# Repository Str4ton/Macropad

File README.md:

# Macropad
A 12-key macropad with 2 rotary encoders using the Arduino Leonardo Micro Pro microcontroler, designed in KiCad.

The schematic can be found in the [MacroPad.pdf](https://github.com/Str4ton/Macropad/blob/main/MacroPad.pdf) file.

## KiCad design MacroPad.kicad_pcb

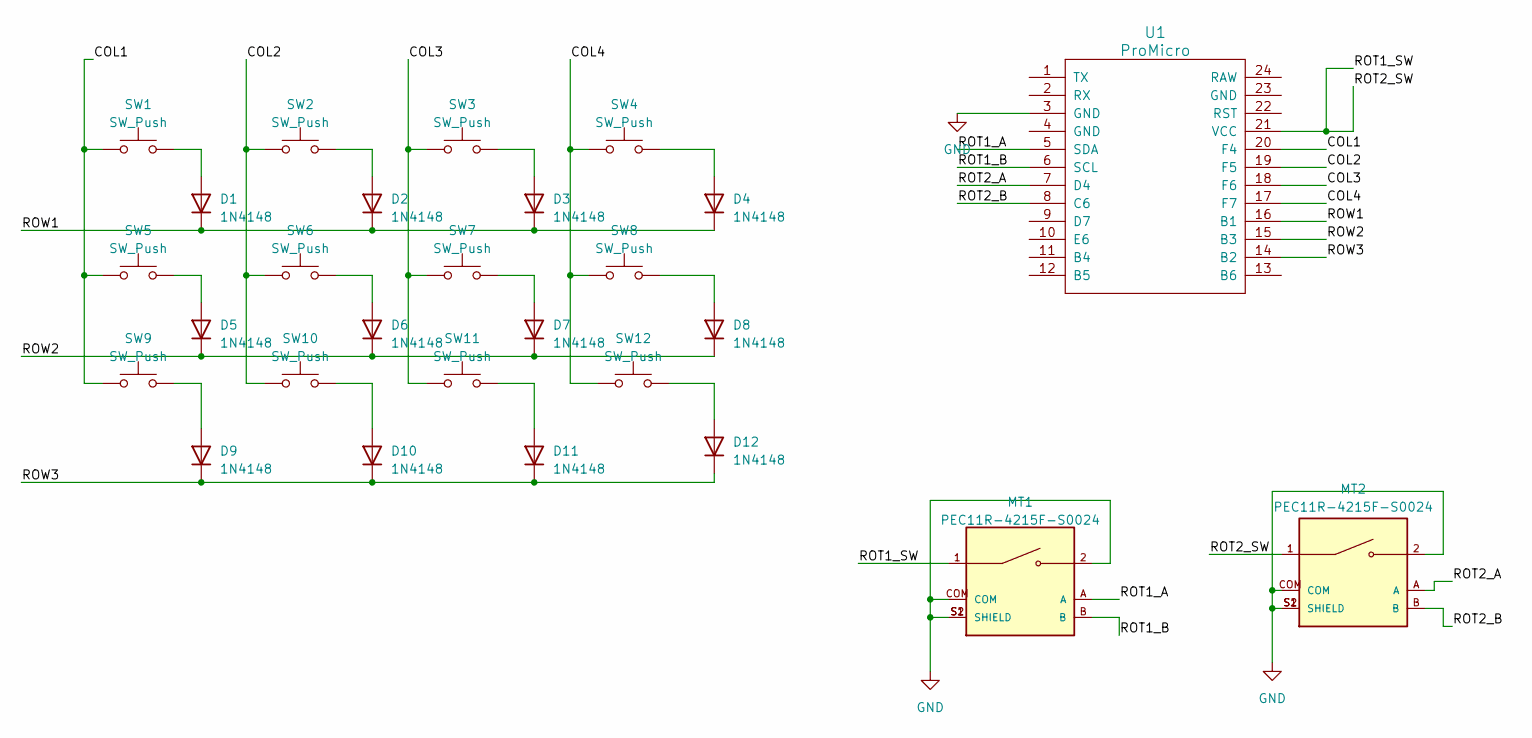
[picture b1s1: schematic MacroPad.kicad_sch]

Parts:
D1, D2, D3, D4, D5, D6, D7, D8, D9, D10, D11, D12: 1N4148; D_DO-35_SOD27_P7.62mm_Horizontal
MT1, MT2: PEC11R-4215F-S0024; XDCR_PEC11R-4215F-S0024; PARTREV Rev. 09/19
SW1, SW2, SW3, SW4, SW5, SW6, SW7, SW8, SW9, SW10, SW11, SW12: SW_Push; SW_Cherry_MX_1.00u_Plate
U1: ProMicro

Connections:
/COL1: SW1.1, SW5.1, SW9.1, U1.20 (F4)
/COL2: SW2.1, SW6.1, SW10.1, U1.19 (F5)
/COL3: SW3.1, SW7.1, SW11.1, U1.18 (F6)
/COL4: SW4.1, SW8.1, SW12.1, U1.17 (F7)
/ROT1_A: MT1.A, U1.5 (SDA)
/ROT1_B: MT1.B, U1.6 (SCL)
/ROT1_SW: MT1.1, MT2.1, U1.21 (VCC)
/ROT2_A: MT2.A, U1.7 (D4)
/ROT2_B: MT2.B, U1.8 (C6)
/ROW1: D1.1 (K), D2.1 (K), D3.1 (K), D4.1 (K), U1.16 (B1)
/ROW2: D5.1 (K), D6.1 (K), D7.1 (K), D8.1 (K), U1.15 (B3)
/ROW3: D9.1 (K), D10.1 (K), D11.1 (K), D12.1 (K), U1.14 (B2)
GND: MT1.2, MT1.COM, MT1.S1 (SHIELD), MT1.S2 (SHIELD), MT2.2, MT2.COM, MT2.S1 (SHIELD), MT2.S2 (SHIELD), U1.3 (GND)
unnamed: D1.2 (A), SW1.2
unnamed: D2.2 (A), SW2.2
unnamed: D3.2 (A), SW3.2
unnamed: D4.2 (A), SW4.2
unnamed: D5.2 (A), SW5.2
unnamed: D6.2 (A), SW6.2
unnamed: D7.2 (A), SW7.2
unnamed: D8.2 (A), SW8.2
unnamed: D9.2 (A), SW9.2
unnamed: D10.2 (A), SW10.2
unnamed: D11.2 (A), SW11.2
unnamed: D12.2 (A), SW12.2

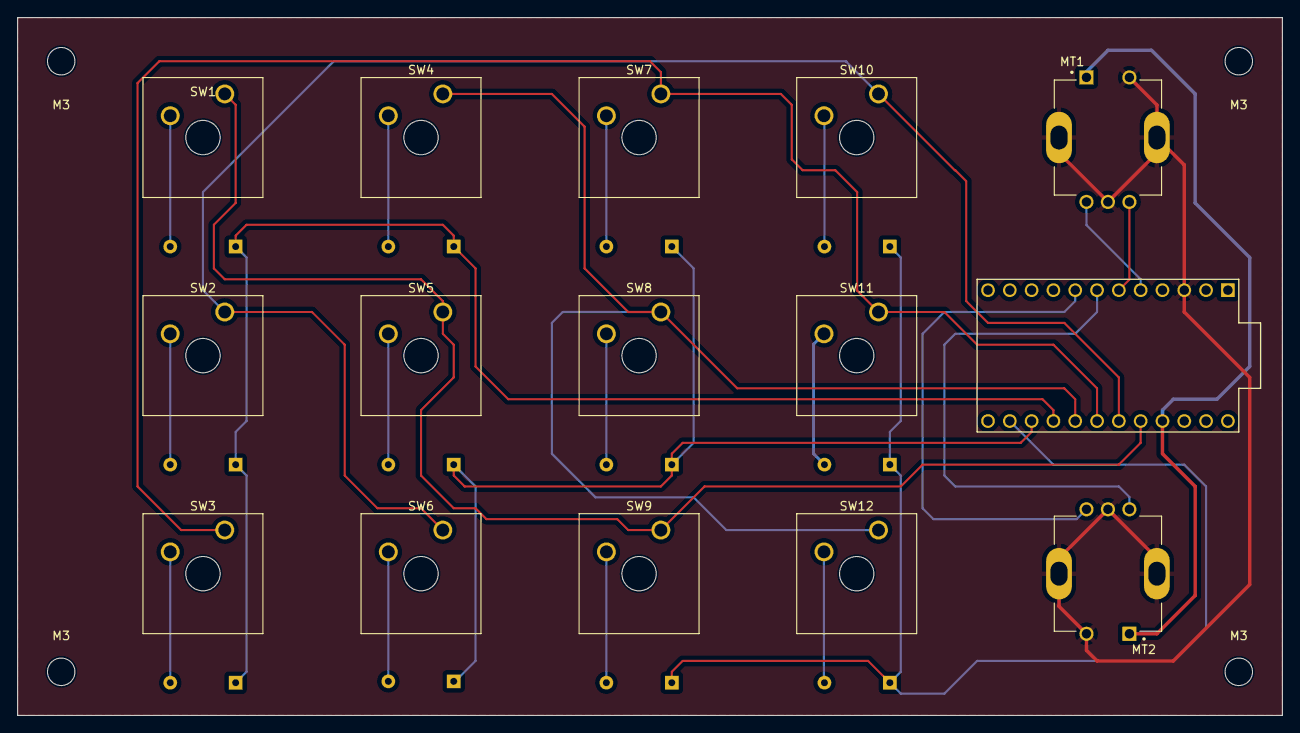
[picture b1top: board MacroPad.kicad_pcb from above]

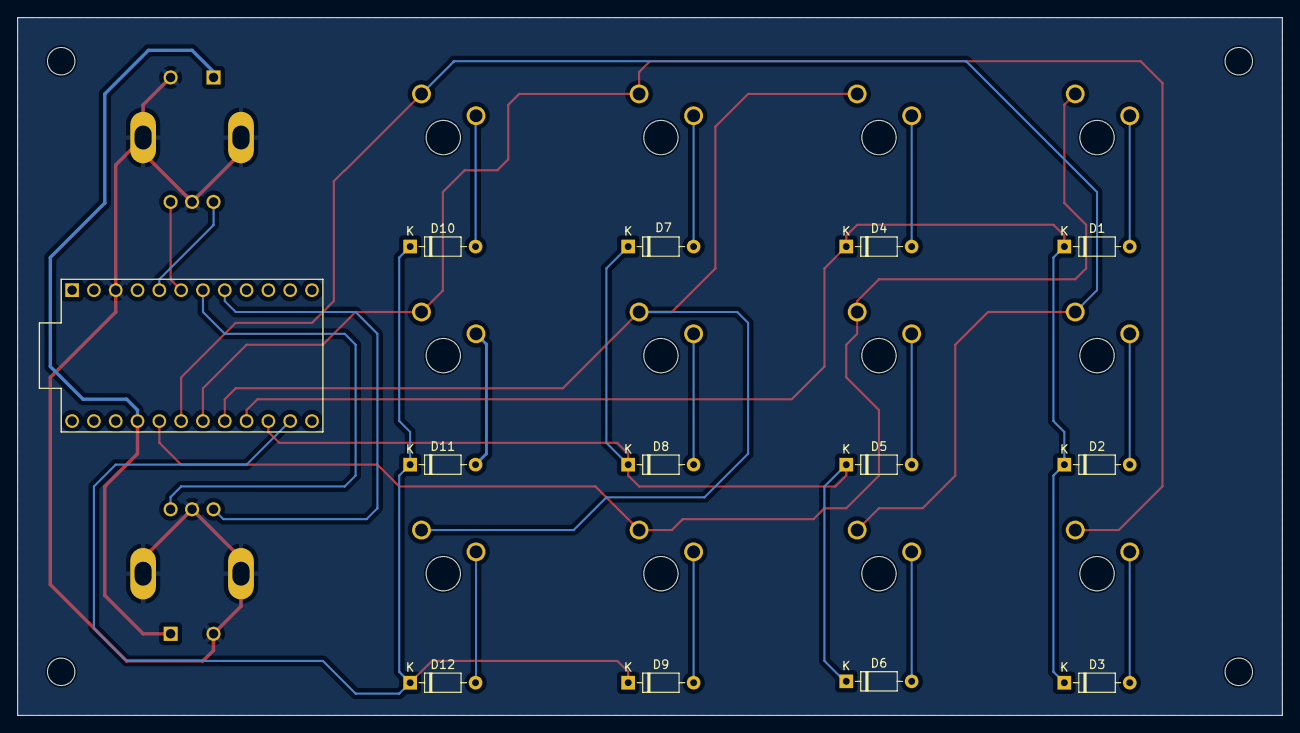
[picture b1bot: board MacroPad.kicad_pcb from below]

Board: 2 copper layers, 147.3 x 81.3 mm, 31 parts (12 on the bottom side), 25 nets.

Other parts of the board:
M3, M3#2, M3#3, M3#4: M3; MountingHole_3.2mm_M3
